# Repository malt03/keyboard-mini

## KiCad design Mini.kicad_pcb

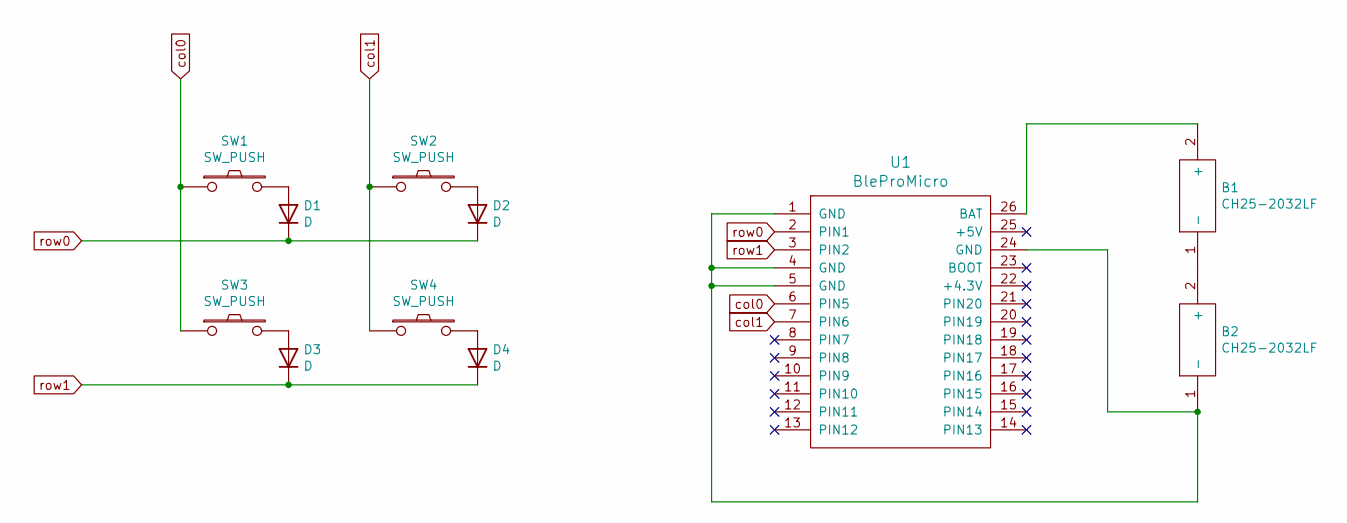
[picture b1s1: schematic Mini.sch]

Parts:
B1, B2: CH25-2032LF; CH252032LF; Manufacturer_Part_Number CH25-2032LF
D1, D2, D3, D4: D; D3_TH
SW1, SW2, SW3, SW4: SW_PUSH; Kailh_socket_MX
U1: BleProMicro; BLEMicroPro_reversed

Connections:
unnamed: B1.1 (-), B2.2 (+)
unnamed: B1.2 (+), U1.26 (BAT)
unnamed: B2.1 (-), U1.1 (GND), U1.4 (GND), U1.5 (GND), U1.24 (GND)
unnamed: D1.2 (A), SW1.2
unnamed: D2.2 (A), SW2.2
unnamed: D3.2 (A), SW3.2
unnamed: D4.2 (A), SW4.2
col0: SW1.1, SW3.1, U1.6 (PIN5)
col1: SW2.1, SW4.1, U1.7 (PIN6)
row0: D1.1 (K), D2.1 (K), U1.2 (PIN1)
row1: D3.1 (K), D4.1 (K), U1.3 (PIN2)

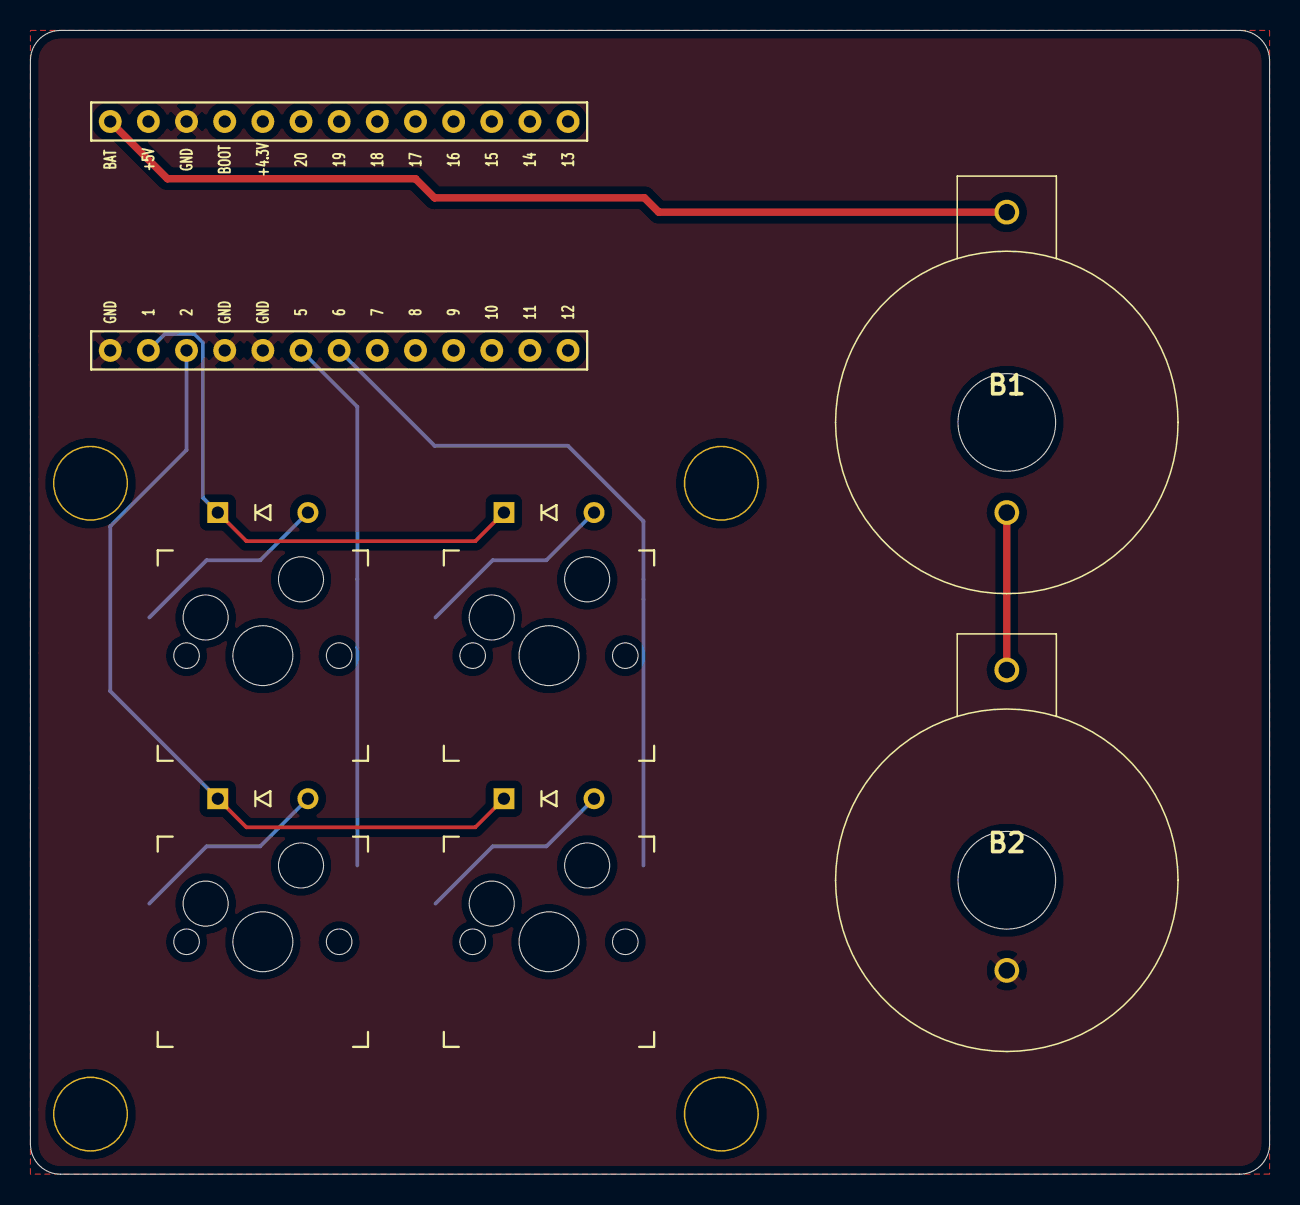
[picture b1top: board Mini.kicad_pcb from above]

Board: 2 copper layers, 82.5 x 76.2 mm, 15 parts (0 on the bottom side), 11 nets.

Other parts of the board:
Ref**: Val**; HOLE
Ref**#2, Ref**#3, Ref**#4: Val**; HOLE

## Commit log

2020-08-07 first
